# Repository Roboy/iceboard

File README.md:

# bldc_motorboard
awesome motorboard for myoFamily muscles

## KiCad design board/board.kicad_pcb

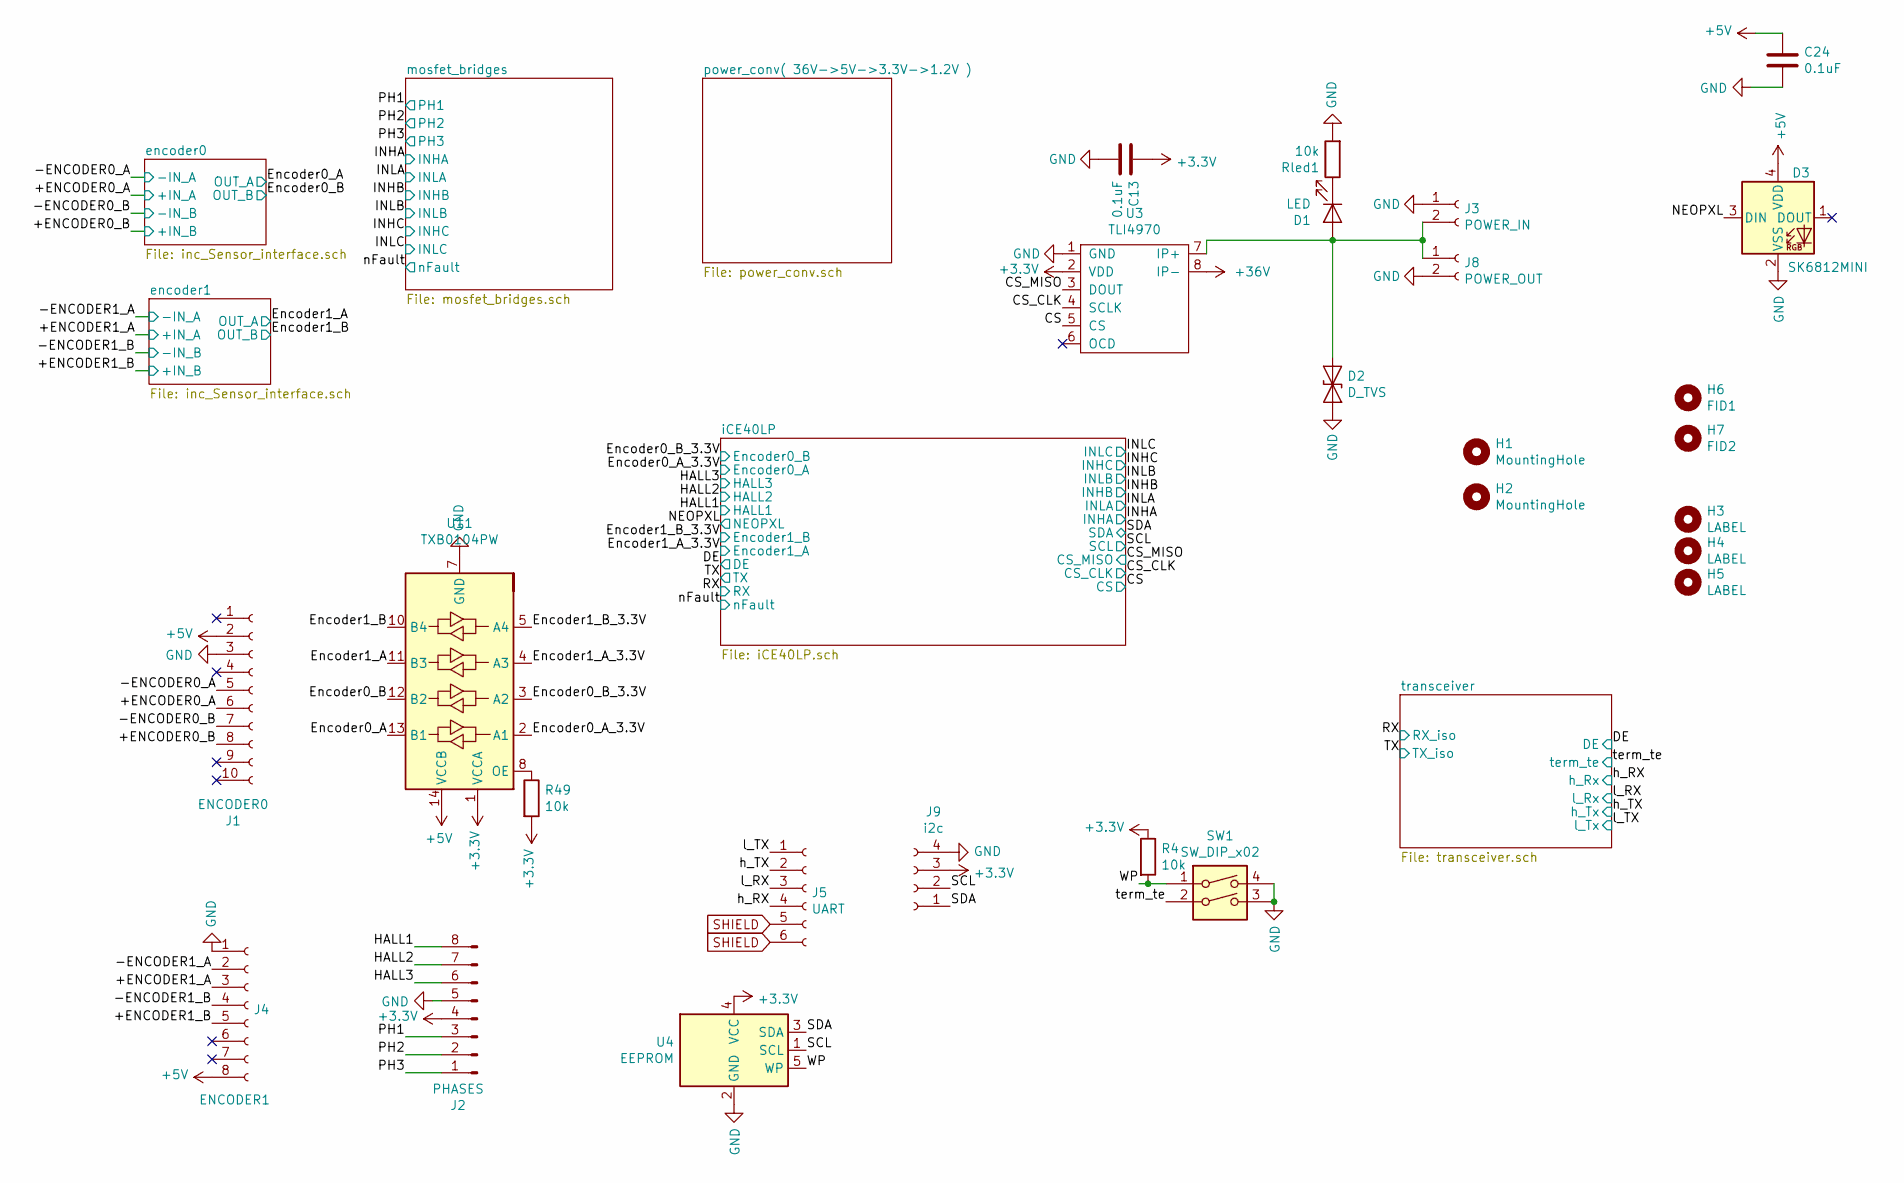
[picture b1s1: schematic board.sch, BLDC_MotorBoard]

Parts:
C13, C24: 0.1uF; C_0402_1005Metric
D1: LED; LED_0603_1608Metric
D2: D_TVS; D_0603_1608Metric
D3: SK6812MINI; LED_SK6812MINI_PLCC4_3.5x3.5mm_P1.75mm
H1, H2: MountingHole; MountingHole_2.2mm_M2
H3: LABEL; R1_ear_silk_5.5mm
H4: LABEL; R1_eyes_mask_5.5mm
H5: LABEL; R1_face_mask_5.5mm
H6: FID1; Fiducial_0.5mm_Dia_1mm_Outer
H7: FID2; Fiducial_0.5mm_Dia_1mm_Outer
J1: ENCODER0; micro_match_female_10pos_SMT
J2: PHASES; PinHeader_1x08_P2.54mm_Vertical
J3: POWER_IN; Wago_2060_2_SMD
J4: ENCODER1; micro_match_female_8pos_SMT
J5: UART; TE-Connectivity_Micro-Match_connector_02x03_Pitch_1.27mm
J8: POWER_OUT; Wago_2060_2_SMD
J9: i2c; TE-Connectivity_Micro-Match_connector_02x02_Pitch_1.27mm
R4, R49: 10k; R_0402_1005Metric
Rled1: 10k; R_0402_1005Metric
SW1: SW_DIP_x02; SW_DIP_SPSTx02_Slide_Copal_CHS-02B_W7.62mm_P1.27mm
U3: TLI4970
U4: EEPROM; SOT-23-5
U11: TXB0104PW; TSSOP-14_4.4x5mm_P0.65mm

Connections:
+5V: C24.1, D3.4 (VDD), J1.2, J4.8, U11.14 (VCCB); also elsewhere on the board
+36V: U3.8 (IP-); also elsewhere on the board
/+ENCODER0_A: J1.6; also elsewhere on the board
/+ENCODER0_B: J1.8; also elsewhere on the board
/+ENCODER1_A: J4.3; also elsewhere on the board
/+ENCODER1_B: J4.5; also elsewhere on the board
/-ENCODER0_A: J1.5; also elsewhere on the board
/-ENCODER0_B: J1.7; also elsewhere on the board
/-ENCODER1_A: J4.2; also elsewhere on the board
/-ENCODER1_B: J4.4; also elsewhere on the board
/CS: U3.5 (CS); also elsewhere on the board
/CS_CLK: U3.4 (SCLK); also elsewhere on the board
/CS_MISO: U3.3 (DOUT); also elsewhere on the board
/Encoder0_A: U11.13 (B1); also elsewhere on the board
/Encoder0_A_3.3V: U11.2 (A1); also elsewhere on the board
/Encoder0_B: U11.12 (B2); also elsewhere on the board
/Encoder0_B_3.3V: U11.3 (A2); also elsewhere on the board
/Encoder1_A: U11.11 (B3); also elsewhere on the board
/Encoder1_A_3.3V: U11.4 (A3); also elsewhere on the board
/Encoder1_B: U11.10 (B4); also elsewhere on the board
/Encoder1_B_3.3V: U11.5 (A4); also elsewhere on the board
/HALL1: J2.8; also elsewhere on the board
/HALL2: J2.7; also elsewhere on the board
/HALL3: J2.6; also elsewhere on the board
/NEOPXL: D3.3 (DIN); also elsewhere on the board
/PH1: J2.3; also elsewhere on the board
/PH2: J2.2; also elsewhere on the board
/PH3: J2.1; also elsewhere on the board
/SCL: J9.2, U4.1 (SCL); also elsewhere on the board
/SDA: J9.1, U4.3 (SDA); also elsewhere on the board
/WP: R4.2, SW1.1, U4.5 (WP)
/h_RX: J5.4; also elsewhere on the board
/h_TX: J5.2; also elsewhere on the board
/l_RX: J5.3; also elsewhere on the board
/l_TX: J5.1; also elsewhere on the board
/term_te: SW1.2; also elsewhere on the board
GND: C13.2, C24.2, D2.2 (A2), D3.2 (VSS), J1.3, J2.5, J3.1, J4.1, J8.2, J9.4, Rled1.2, SW1.3, SW1.4, U3.1 (GND), U4.2 (GND), U11.7 (GND); also elsewhere on the board
unnamed: D1.1 (K), Rled1.1
unnamed: D1.2 (A), D2.1 (A1), J3.2, J8.1, U3.7 (IP+)
unnamed: R49.1, U11.8 (OE)
SHIELD: J5.5, J5.6; also elsewhere on the board

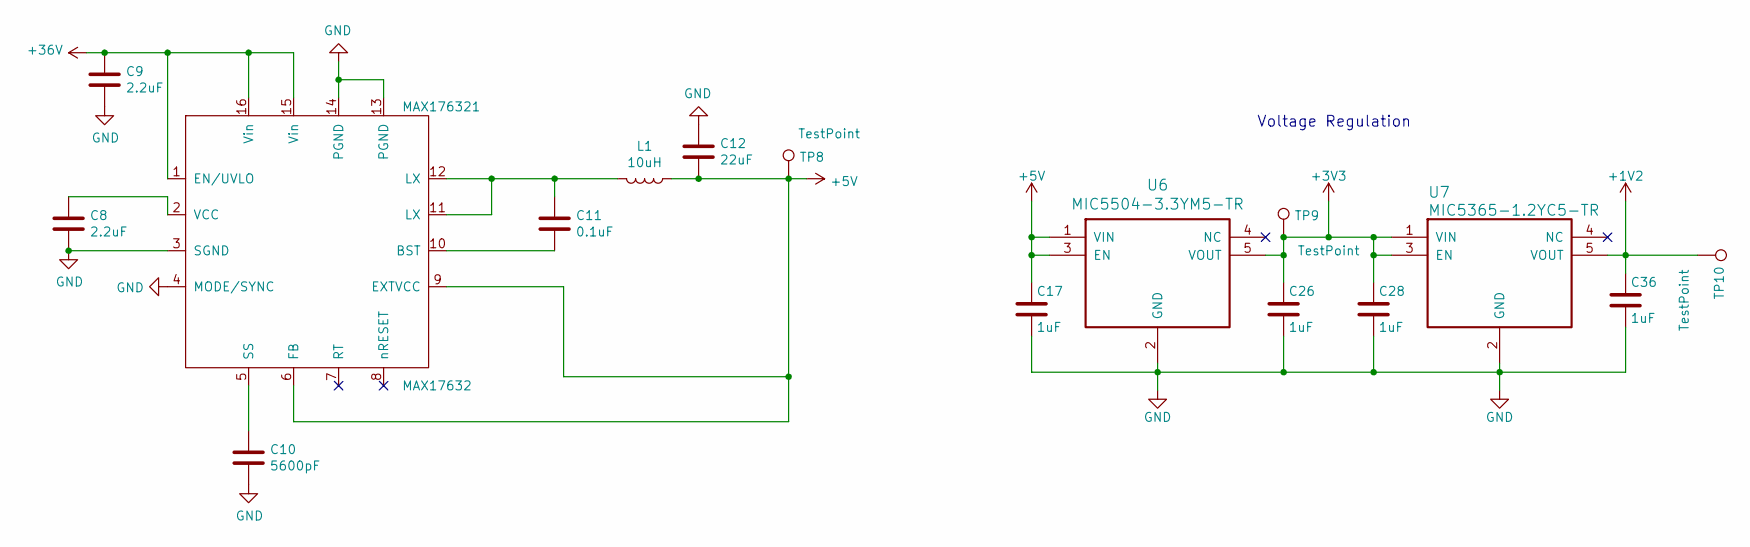
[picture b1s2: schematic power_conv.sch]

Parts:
C8, C9: 2.2uF; C_0603_1608Metric
C10: 5600pF; C_0402_1005Metric
C11: 0.1uF; C_0402_1005Metric
C12: 22uF; C_0805_2012Metric
C17, C26, C28, C36: 1uF; C_0402_1005Metric
L1: 10uH; XAL5050-103MEC
MAX176321: MAX17632; QFN-16-1EP_3x3mm_Pitch0.5mm
TP8, TP9, TP10: TestPoint; TestPoint_Pad_D1.0mm
U6: MIC5504-3.3YM5-TR; SC70-5
U7: MIC5365-1.2YC5-TR; SC-70-C5

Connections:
+1V2: C36.1, TP10.1, U7.5 (VOUT); also elsewhere on the board
+5V: C12.2, C17.1, L1.1, MAX176321.6 (FB), MAX176321.9 (EXTVCC), TP8.1, U6.1 (VIN), U6.3 (EN); also elsewhere on the board
+36V: C9.1, MAX176321.1 (EN/UVLO), MAX176321.15 (Vin), MAX176321.16 (Vin); also elsewhere on the board
GND: C8.2, C9.2, C10.2, C12.1, C17.2, C26.2, C28.2, C36.2, MAX176321.3 (SGND), MAX176321.4 (MODE/SYNC), MAX176321.13 (PGND), MAX176321.14 (PGND), U6.2 (GND), U7.2 (GND); also elsewhere on the board
unnamed: C8.1, MAX176321.2 (VCC)
unnamed: C10.1, MAX176321.5 (SS)
unnamed: C11.1, L1.2, MAX176321.11 (LX), MAX176321.12 (LX)
unnamed: C11.2, MAX176321.10 (BST)
unnamed 107: U6.4 (NC); also elsewhere on the board

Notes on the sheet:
Voltage Regulation

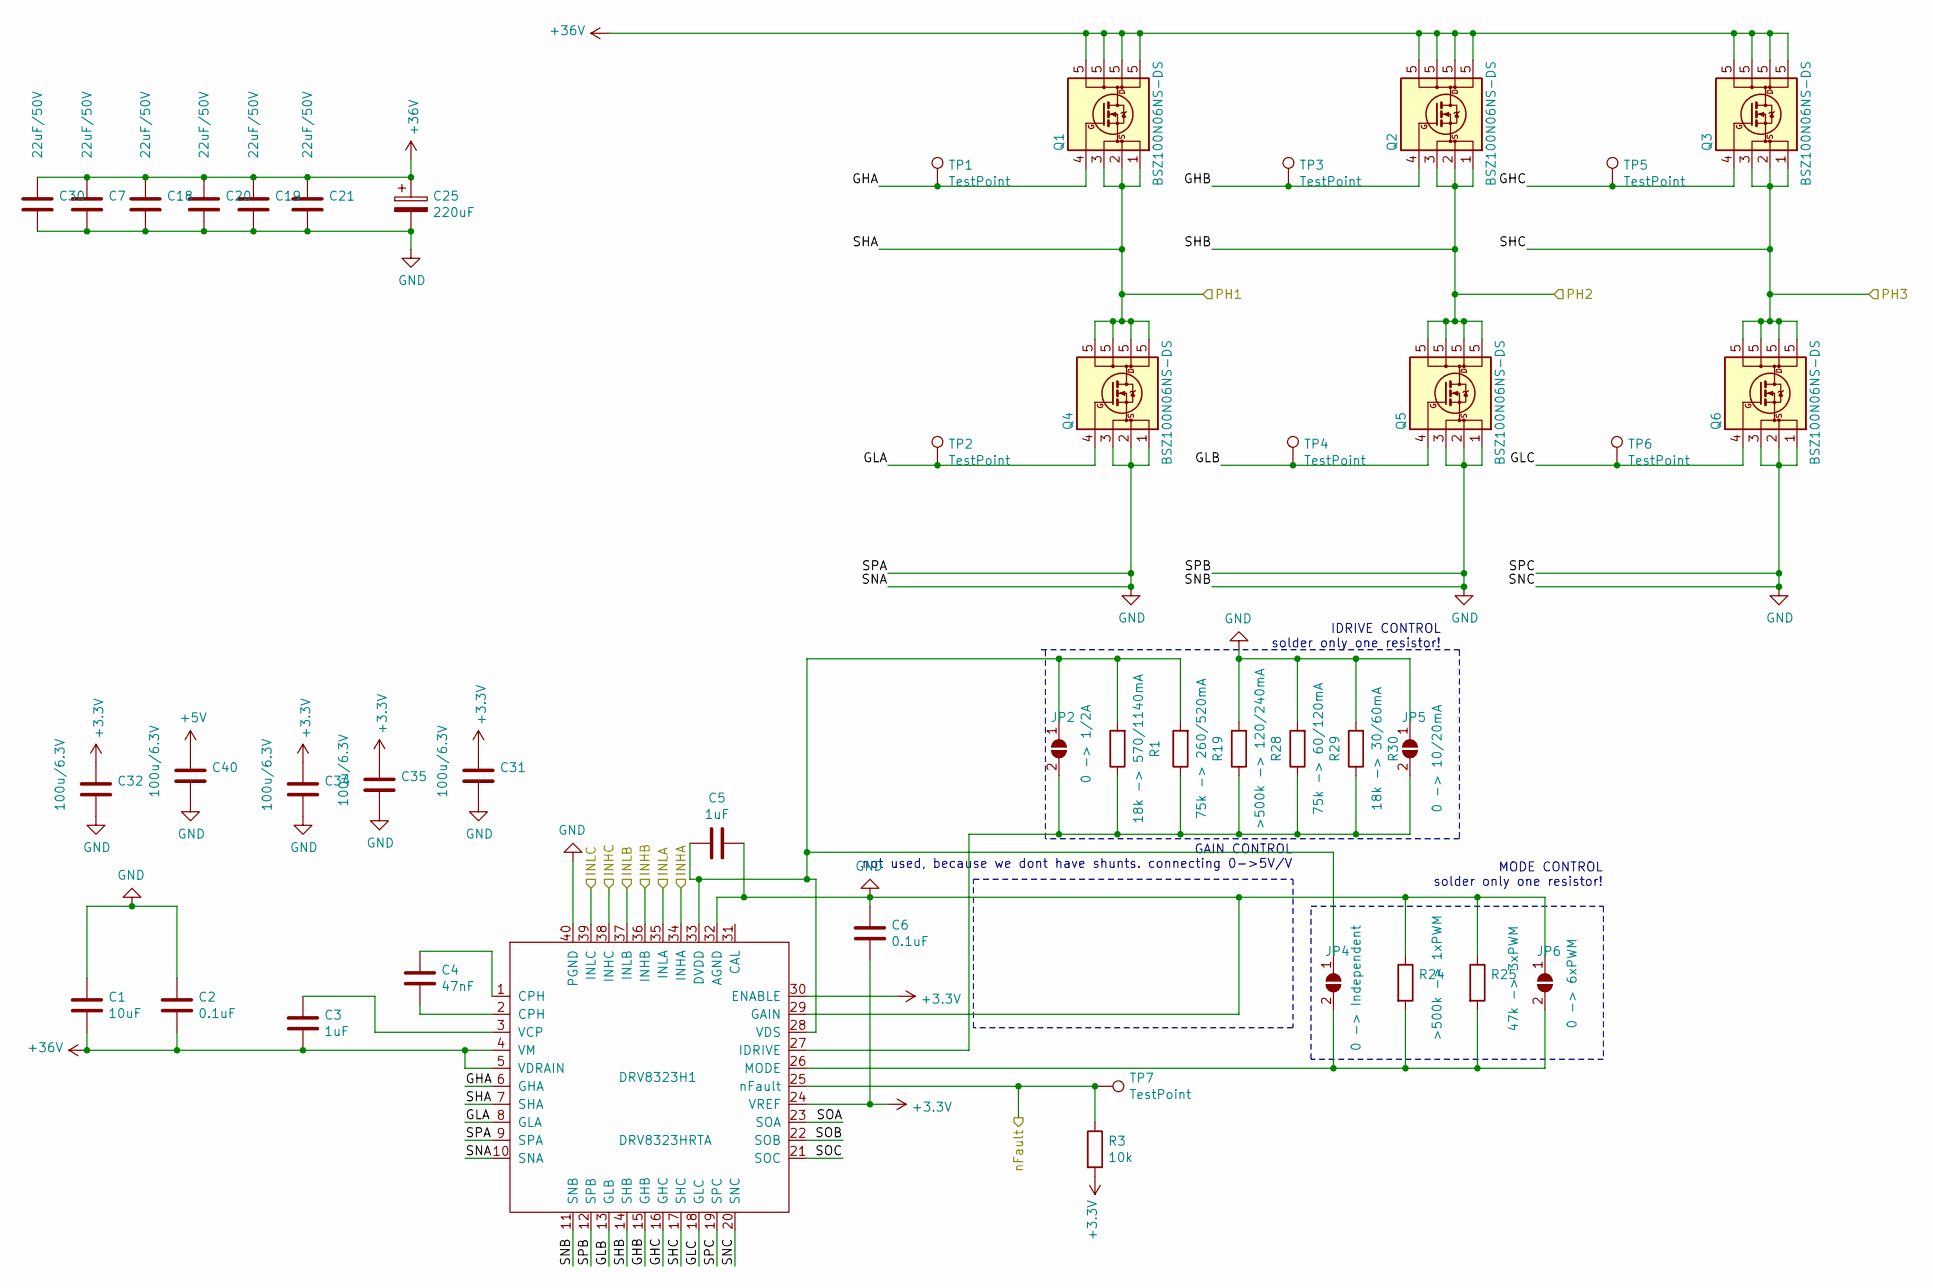
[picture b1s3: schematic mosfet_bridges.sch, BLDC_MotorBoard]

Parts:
C1: 10uF; C_0402_1005Metric
C2, C6: 0.1uF; C_0402_1005Metric
C3, C5: 1uF; C_0402_1005Metric
C4: 47nF; C_0402_1005Metric
C7, C18, C19, C20, C21, C30: 22uF/50V; C_0805_2012Metric
C25: 220uF; CP_Elec_8x10
C31, C32, C34, C35, C40: 100u/6.3V; C_0805_2012Metric
DRV8323H1: DRV8323HRTA; QFN-40-1EP_6x6mm_Pitch0.5mm
JP2: 0 -> 1/2A; SolderJumper-2_P1.3mm_Open_Pad1.0x1.5mm
JP4: 0 -> Independent; SolderJumper-2_P1.3mm_Open_Pad1.0x1.5mm
JP5: 0 -> 10/20mA; SolderJumper-2_P1.3mm_Open_Pad1.0x1.5mm
JP6: 0 -> 6xPWM; SolderJumper-2_P1.3mm_Open_Pad1.0x1.5mm
Q1, Q2, Q3, Q4, Q5, Q6: BSZ100N06NS-DS; VSON-8_3.3x3.3mm_P0.65mm_NexFET
R1: 18k -> 570/1140mA; R_0402_1005Metric
R3: 10k; R_0402_1005Metric
R19: 75k -> 260/520mA; R_0402_1005Metric
R24: >500k -> 1xPWM; R_0402_1005Metric
R25: 47k -> 3xPWM; R_0402_1005Metric
R28: >500k -> 120/240mA; R_0402_1005Metric
R29: 75k -> 60/120mA; R_0402_1005Metric
R30: 18k -> 30/60mA; R_0402_1005Metric
TP1, TP2, TP3, TP4, TP5, TP6, TP7: TestPoint; TestPoint_Pad_D1.0mm

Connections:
+5V: C40.1; also elsewhere on the board
+36V: C1.2, C2.2, C3.2, C7.1, C18.1, C19.1, C20.1, C21.1, C25.1, C30.1, DRV8323H1.4 (VM), DRV8323H1.5 (VDRAIN), Q1.5 (D), Q2.5 (D), Q3.5 (D); also elsewhere on the board
/INHA: DRV8323H1.34 (INHA); also elsewhere on the board
/INHB: DRV8323H1.36 (INHB); also elsewhere on the board
/INHC: DRV8323H1.38 (INHC); also elsewhere on the board
/INLA: DRV8323H1.35 (INLA); also elsewhere on the board
/INLB: DRV8323H1.37 (INLB); also elsewhere on the board
/INLC: DRV8323H1.39 (INLC); also elsewhere on the board
/PH1: DRV8323H1.7 (SHA), Q1.1 (S), Q1.2 (S), Q1.3 (S), Q4.5 (D); also elsewhere on the board
/PH2: DRV8323H1.14 (SHB), Q2.1 (S), Q2.2 (S), Q2.3 (S), Q5.5 (D); also elsewhere on the board
/PH3: DRV8323H1.17 (SHC), Q3.1 (S), Q3.2 (S), Q3.3 (S), Q6.5 (D); also elsewhere on the board
/mosfet_bridges/GHA: DRV8323H1.6 (GHA), Q1.4 (G), TP1.1
/mosfet_bridges/GHB: DRV8323H1.15 (GHB), Q2.4 (G), TP3.1
/mosfet_bridges/GHC: DRV8323H1.16 (GHC), Q3.4 (G), TP5.1
/mosfet_bridges/GLA: DRV8323H1.8 (GLA), Q4.4 (G), TP2.1
/mosfet_bridges/GLB: DRV8323H1.13 (GLB), Q5.4 (G), TP4.1
/mosfet_bridges/GLC: DRV8323H1.18 (GLC), Q6.4 (G), TP6.1
/mosfet_bridges/SOA: DRV8323H1.23 (SOA)
/mosfet_bridges/SOB: DRV8323H1.22 (SOB)
/mosfet_bridges/SOC: DRV8323H1.21 (SOC)
/nFault: DRV8323H1.25 (nFault), R3.1, TP7.1; also elsewhere on the board
GND: C1.1, C2.1, C5.1, C6.1, C7.2, C18.2, C19.2, C20.2, C21.2, C25.2, C30.2, C31.2, C32.2, C34.2, C35.2, C40.2, DRV8323H1.9 (SPA), DRV8323H1.10 (SNA), DRV8323H1.11 (SNB), DRV8323H1.12 (SPB), DRV8323H1.19 (SPC), DRV8323H1.20 (SNC), DRV8323H1.29 (GAIN), DRV8323H1.32 (AGND), DRV8323H1.40 (PGND), JP5.1 (A), JP6.1 (A), Q4.1 (S), Q4.2 (S), Q4.3 (S), Q5.1 (S), Q5.2 (S), Q5.3 (S), Q6.1 (S), Q6.2 (S), Q6.3 (S), R24.1, R25.1, R28.2, R29.2, R30.2; also elsewhere on the board
unnamed: C3.1, DRV8323H1.3 (VCP)
unnamed: C4.1, DRV8323H1.1 (CPH)
unnamed: C4.2, DRV8323H1.2 (CPH)
unnamed: C5.2, DRV8323H1.28 (VDS), DRV8323H1.33 (DVDD), JP2.1 (A), JP4.1 (A), R1.2, R19.2
unnamed: DRV8323H1.26 (MODE), JP4.2 (B), JP6.2 (B), R24.2, R25.2
unnamed: DRV8323H1.27 (IDRIVE), JP2.2 (B), JP5.2 (B), R1.1, R19.1, R28.1, R29.1, R30.1

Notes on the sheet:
MODE CONTROL solder only one resistor!
GAIN CONTROL not used, because we dont have shunts. connecting 0->5V/V
IDRIVE CONTROL solder only one resistor!

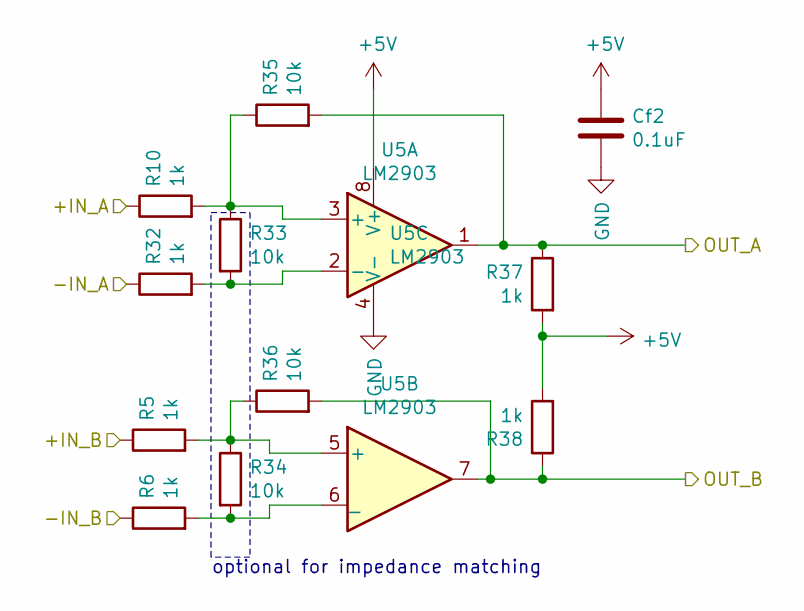
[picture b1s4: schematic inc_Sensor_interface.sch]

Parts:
Cf1: 0.1uF; C_0402_1005Metric
R7, R8, R9, R11, R16, R17: 1k; R_0402_1005Metric
R12, R13, R14, R15: 10k; R_0402_1005Metric
U2: LM2903; TSSOP-8_4.4x3mm_P0.65mm

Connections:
+5V: Cf1.1, R16.2, R17.2, U2.8 (V+); also elsewhere on the board
/+ENCODER0_A: R7.1; also elsewhere on the board
/+ENCODER0_B: R8.1; also elsewhere on the board
/-ENCODER0_A: R11.1; also elsewhere on the board
/-ENCODER0_B: R9.1; also elsewhere on the board
/Encoder0_A: R14.2, R16.1, U2.1; also elsewhere on the board
/Encoder0_B: R15.2, R17.1, U2.7; also elsewhere on the board
GND: Cf1.2, U2.4 (V-); also elsewhere on the board
unnamed: R11.2, R12.2, U2.2 (-)
unnamed: R7.2, R12.1, R14.1, U2.3 (+)
unnamed: R8.2, R13.1, R15.1, U2.5 (+)
unnamed: R9.2, R13.2, U2.6 (_)

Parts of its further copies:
Cf2, Cf3: 0.1uF; C_0402_1005Metric
R5, R6, R10, R32, R37, R38: 1k; R_0402_1005Metric
R33, R34, R35, R36: 10k; R_0402_1005Metric
U5: LM2903; TSSOP-8_4.4x3mm_P0.65mm

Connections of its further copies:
+5V: Cf2.1, R37.2, R38.2, U5.8 (V+); also elsewhere on the board
/+ENCODER1_A: R10.1; also elsewhere on the board
/+ENCODER1_B: R5.1; also elsewhere on the board
/-ENCODER1_A: R32.1; also elsewhere on the board
/-ENCODER1_B: R6.1; also elsewhere on the board
/Encoder1_A: R35.2, R37.1, U5.1; also elsewhere on the board
/Encoder1_B: R36.2, R38.1, U5.7; also elsewhere on the board
GND: Cf2.2, U5.4 (V-); also elsewhere on the board
unnamed: R10.2, R33.1, R35.1, U5.3 (+)
unnamed: R32.2, R33.2, U5.2 (-)
unnamed: R5.2, R34.1, R36.1, U5.5 (+)
unnamed: R6.2, R34.2, U5.6 (_)

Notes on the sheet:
optional for impedance matching

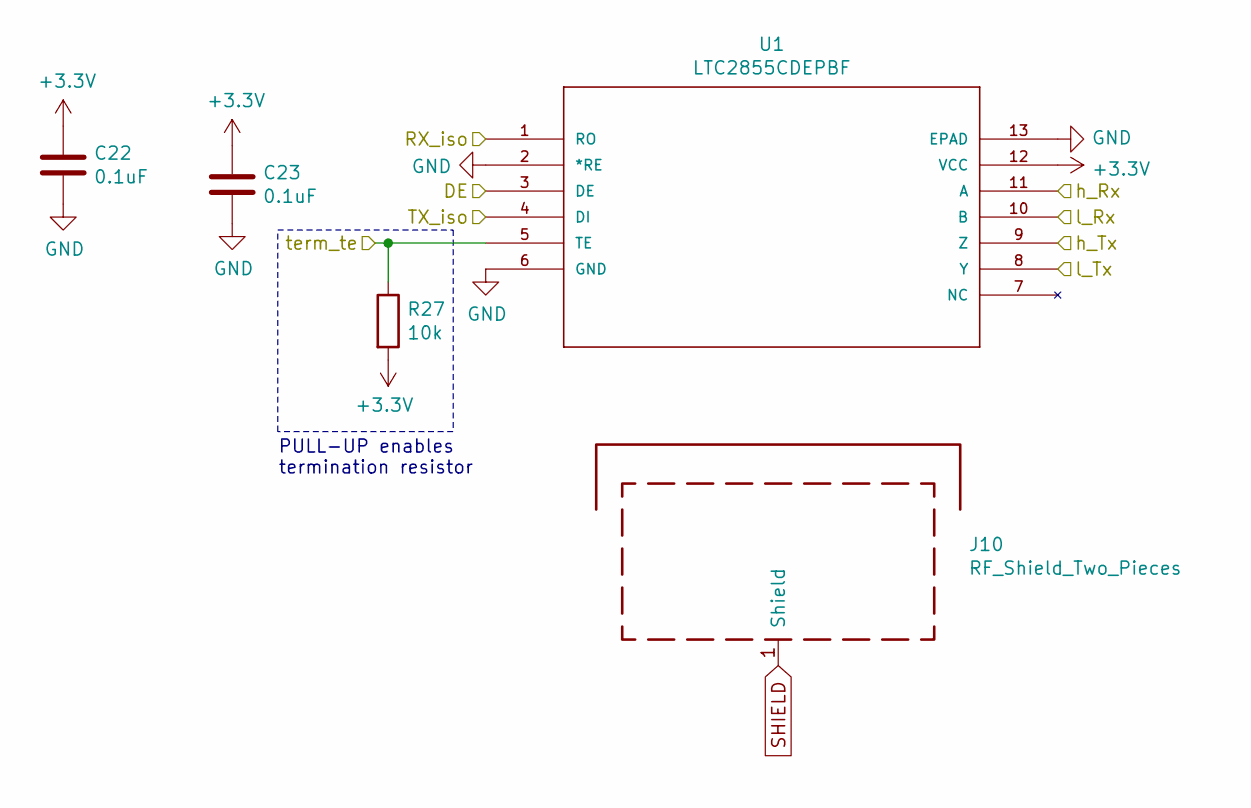
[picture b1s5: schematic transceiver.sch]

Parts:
C22, C23: 0.1uF; C_0402_1005Metric
J10: RF_Shield_Two_Pieces; Laird_Technologies_BMI-S-201-F_13.66x12.70mm
R27: 10k; R_0402_1005Metric
U1: LTC2855CDEPBF; ltc2855

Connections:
/DE: U1.3 (DE); also elsewhere on the board
/RX: U1.1 (RO); also elsewhere on the board
/TX: U1.4 (DI); also elsewhere on the board
/h_RX: U1.11 (A); also elsewhere on the board
/h_TX: U1.9 (Z); also elsewhere on the board
/l_RX: U1.10 (B); also elsewhere on the board
/l_TX: U1.8 (Y); also elsewhere on the board
/term_te: R27.1, U1.5 (TE); also elsewhere on the board
GND: C22.2, C23.2, U1.2 (*RE), U1.6 (GND), U1.13 (EPAD); also elsewhere on the board
SHIELD: J10.1; also elsewhere on the board

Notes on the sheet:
PULL-UP enables termination resistor

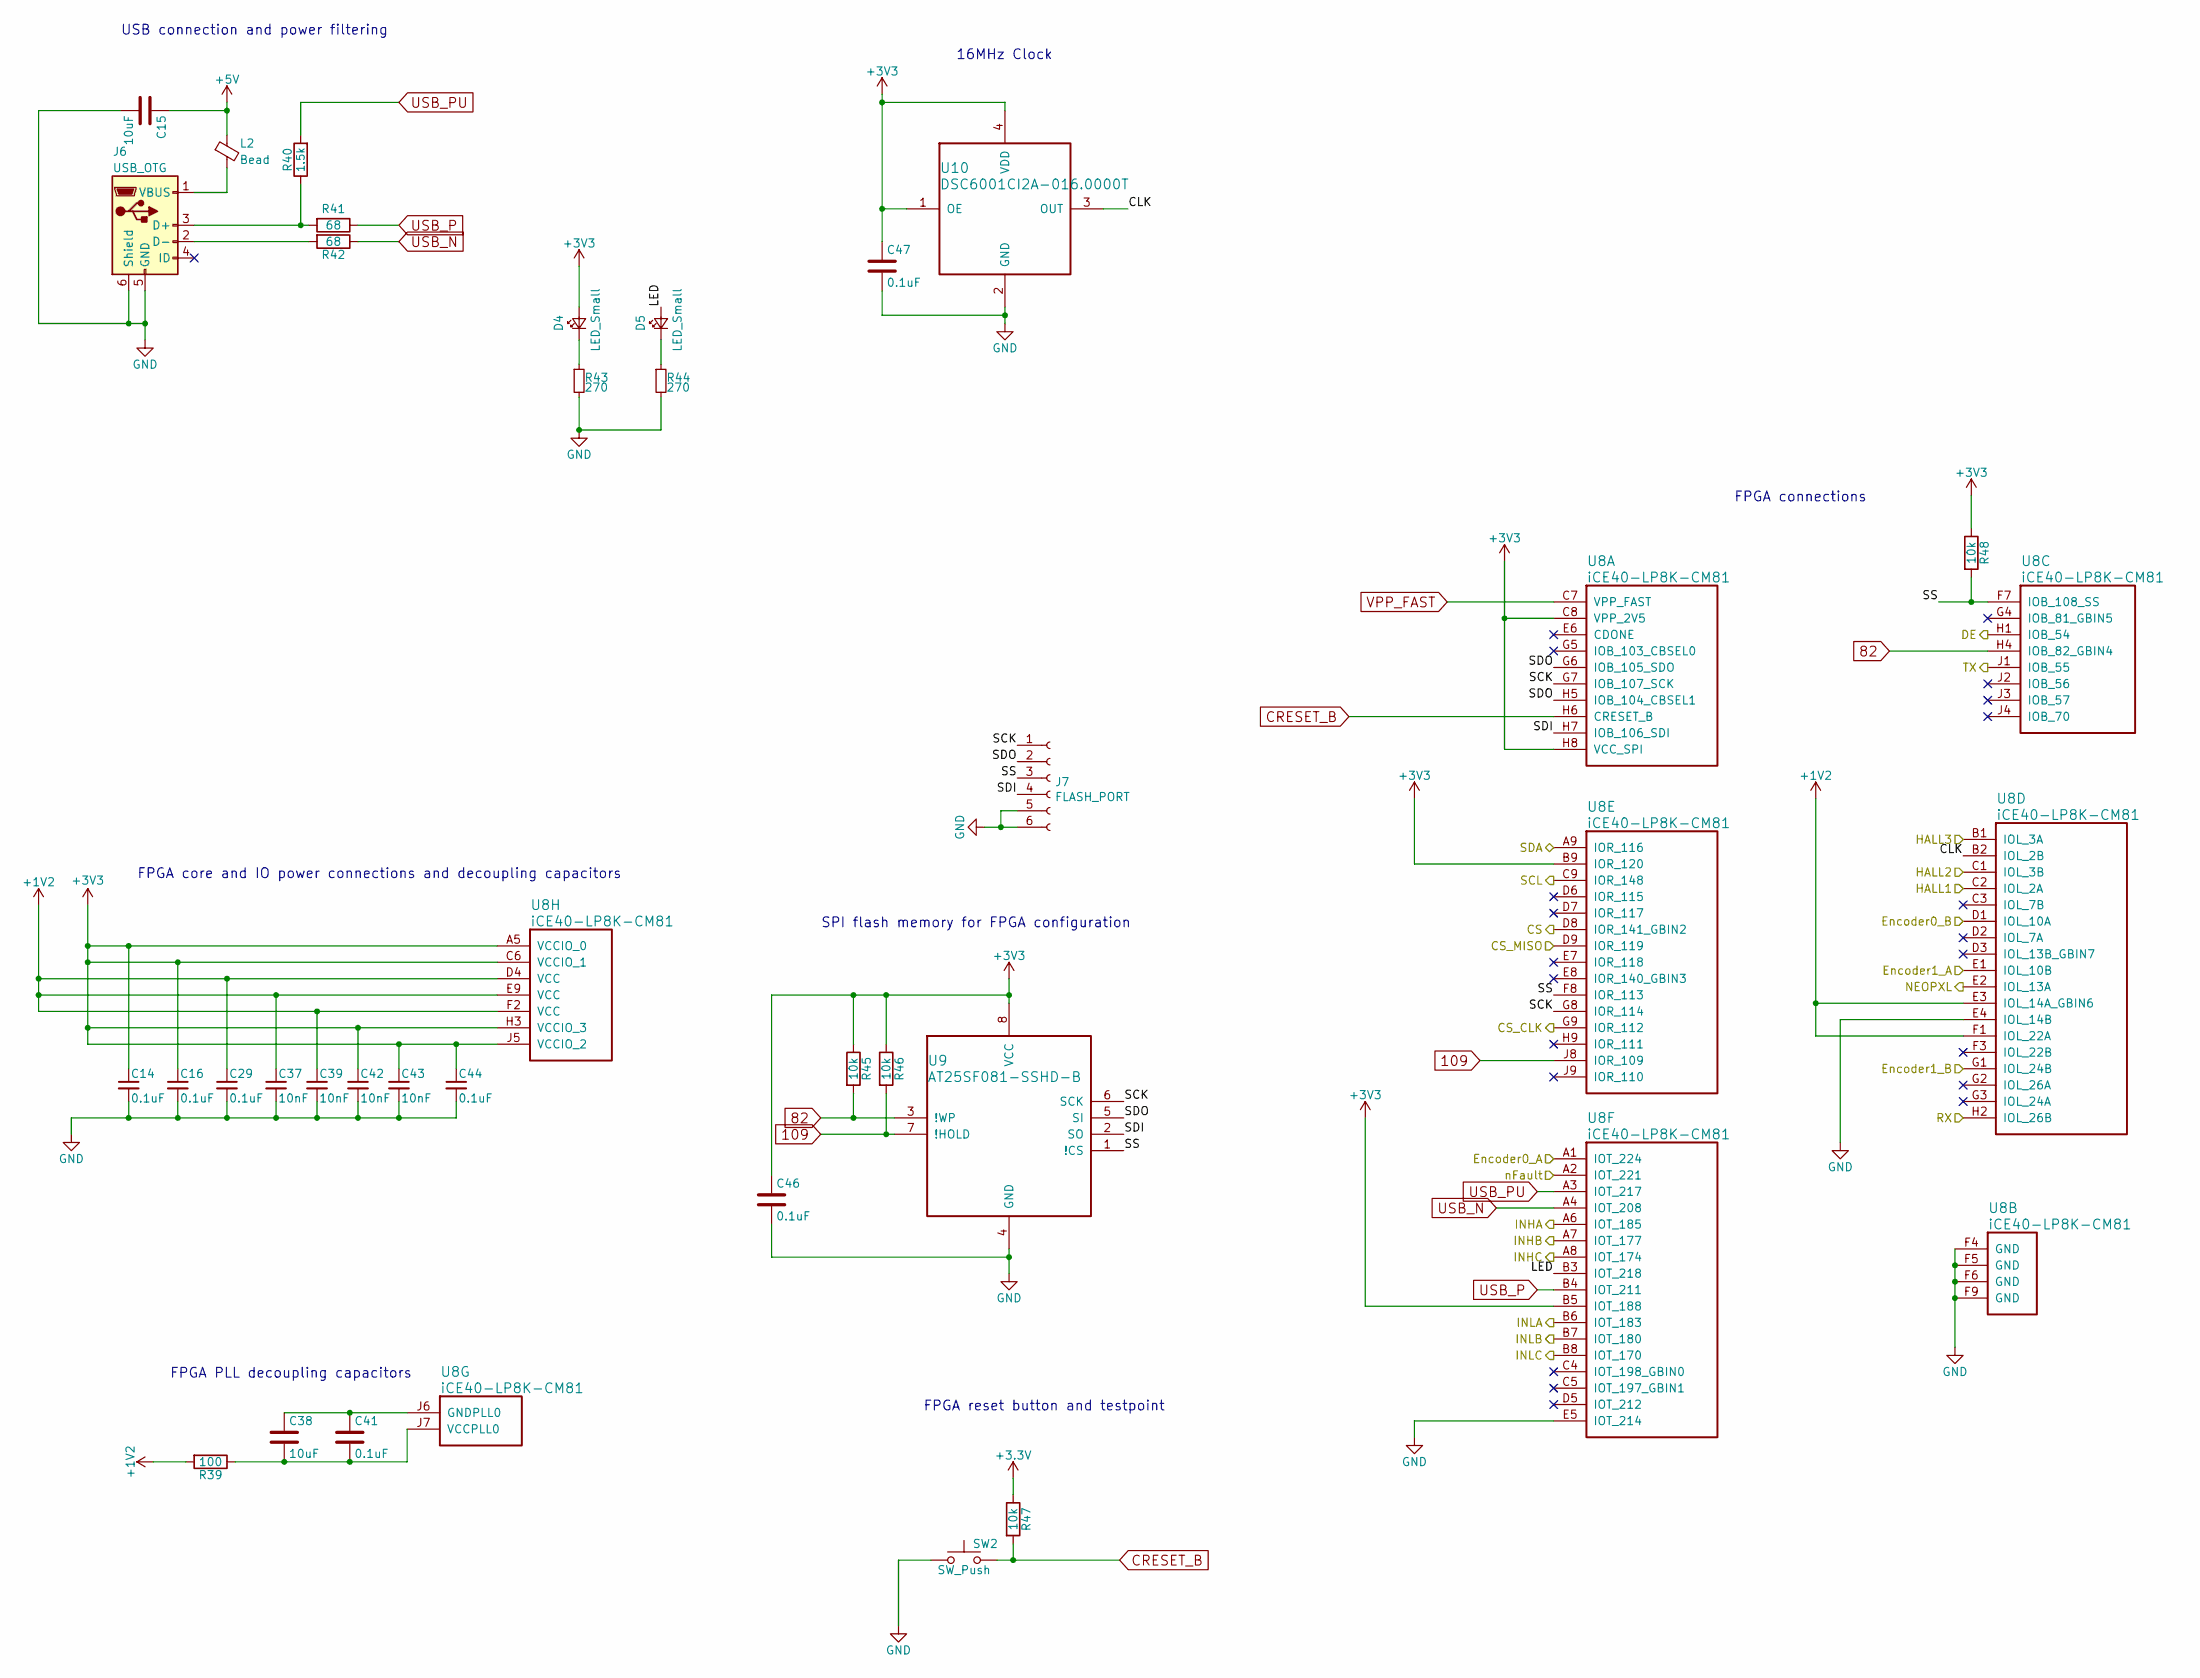
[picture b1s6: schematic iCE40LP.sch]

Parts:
C14, C16, C29, C41, C44, C46, C47: 0.1uF; C_0402_1005Metric
C15, C38: 10uF; C_0402_1005Metric
C37, C39, C42, C43: 10nF; C_0402_1005Metric
D4, D5: LED_Small; LED_0402_1005Metric
J6: USB_OTG; USB_Micro-B_Molex_47346-0001
J7: FLASH_PORT; TC2030-MCP-NL
L2: Bead; L_0603_1608Metric
R39: 100; R_0402_1005Metric
R40: 1.5k; R_0402_1005Metric
R41, R42: 68; R_0402_1005Metric
R43, R44: 270; R_0402_1005Metric
R45, R46, R47, R48: 10k; R_0402_1005Metric
SW2: SW_Push; PTS_810_SMT_Switch
U8: iCE40-LP8K-CM81; CM81
U9: AT25SF081-SSHD-B; SOIC-8_3.9x4.9mm_P1.27mm
U10: DSC6001CI2A-016.0000T; CDFN3225-4LD-PL-1

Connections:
82: R45.2, U8.H4 (IOB_82_GBIN4), U9.3 (!WP)
109: R46.2, U8.J8 (IOR_109), U9.7 (!HOLD)
+1V2: C29.1, C37.1, C39.1, R39.2, U8.D4 (VCC), U8.E3 (IOL_14A_GBIN6), U8.E9 (VCC), U8.F1 (IOL_22A), U8.F2 (VCC); also elsewhere on the board
+5V: C15.1, L2.1; also elsewhere on the board
/CS: U8.D8 (IOR_141_GBIN2); also elsewhere on the board
/CS_CLK: U8.G9 (IOR_112); also elsewhere on the board
/CS_MISO: U8.D9 (IOR_119); also elsewhere on the board
/DE: U8.H1 (IOB_54); also elsewhere on the board
/Encoder0_A_3.3V: U8.A1 (IOT_224); also elsewhere on the board
/Encoder0_B_3.3V: U8.D1 (IOL_10A); also elsewhere on the board
/Encoder1_A_3.3V: U8.E1 (IOL_10B); also elsewhere on the board
/Encoder1_B_3.3V: U8.G1 (IOL_24B); also elsewhere on the board
/HALL1: U8.C2 (IOL_2A); also elsewhere on the board
/HALL2: U8.C1 (IOL_3B); also elsewhere on the board
/HALL3: U8.B1 (IOL_3A); also elsewhere on the board
/INHA: U8.A6 (IOT_185); also elsewhere on the board
/INHB: U8.A7 (IOT_177); also elsewhere on the board
/INHC: U8.A8 (IOT_174); also elsewhere on the board
/INLA: U8.B6 (IOT_183); also elsewhere on the board
/INLB: U8.B7 (IOT_180); also elsewhere on the board
/INLC: U8.B8 (IOT_170); also elsewhere on the board
/NEOPXL: U8.E2 (IOL_13A); also elsewhere on the board
/RX: U8.H2 (IOL_26B); also elsewhere on the board
/SCL: U8.C9 (IOR_148); also elsewhere on the board
/SDA: U8.A9 (IOR_116); also elsewhere on the board
/TX: U8.J1 (IOB_55); also elsewhere on the board
/iCE40LP/CLK: U8.B2 (IOL_2B), U10.3 (OUT)
/iCE40LP/LED: D5.2 (A), U8.B3 (IOT_218)
/iCE40LP/SCK: J7.1, U8.G7 (IOB_107_SCK), U8.G8 (IOR_114), U9.6 (SCK)
/iCE40LP/SDI: J7.4, U8.H7 (IOB_106_SDI), U9.2 (SO)
/iCE40LP/SDO: J7.2, U8.G6 (IOB_105_SDO), U8.H5 (IOB_104_CBSEL1), U9.5 (SI)
/iCE40LP/SS: J7.3, R48.2, U8.F7 (IOB_108_SS), U8.F8 (IOR_113), U9.1 (!CS)
/nFault: U8.A2 (IOT_221); also elsewhere on the board
CRESET_B: R47.2, SW2.2, U8.H6 (CRESET_B)
GND: C14.2, C15.2, C16.2, C29.2, C37.2, C39.2, C42.2, C43.2, C44.2, C46.2, C47.2, J6.5 (GND), J6.6 (Shield), J7.5, J7.6, R43.2, R44.2, SW2.1, U8.E4 (IOL_14B), U8.E5 (IOT_214), U8.F4 (GND), U8.F5 (GND), U8.F6 (GND), U8.F9 (GND), U9.4 (GND), U10.2 (GND); also elsewhere on the board
unnamed: C38.1, C41.1, U8.J6 (GNDPLL0)
unnamed: C38.2, C41.2, R39.1, U8.J7 (VCCPLL0)
unnamed: D4.1 (K), R43.1
unnamed: D5.1 (K), R44.1
unnamed: J6.1 (VBUS), L2.2
unnamed: J6.2 (D-), R42.2
unnamed: J6.3 (D+), R40.1, R41.2
USB_N: R42.1, U8.A4 (IOT_208)
USB_P: R41.1, U8.B4 (IOT_211)
USB_PU: R40.2, U8.A3 (IOT_217)
VPP_FAST: U8.C7 (VPP_FAST)

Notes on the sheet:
FPGA core and IO power connections and decoupling capacitors
FPGA PLL decoupling capacitors
USB connection and power filtering
16MHz Clock
SPI flash memory for FPGA configuration
FPGA reset button and testpoint
FPGA connections

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

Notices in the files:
parts and their libraries:
©2009 ROFA.cz - modified and updated by Robert Darlington ‹rdarlington@gmail.com›
